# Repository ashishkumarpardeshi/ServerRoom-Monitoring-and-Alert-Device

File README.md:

# ServerRoom-Monitoring-and-Alert-Device

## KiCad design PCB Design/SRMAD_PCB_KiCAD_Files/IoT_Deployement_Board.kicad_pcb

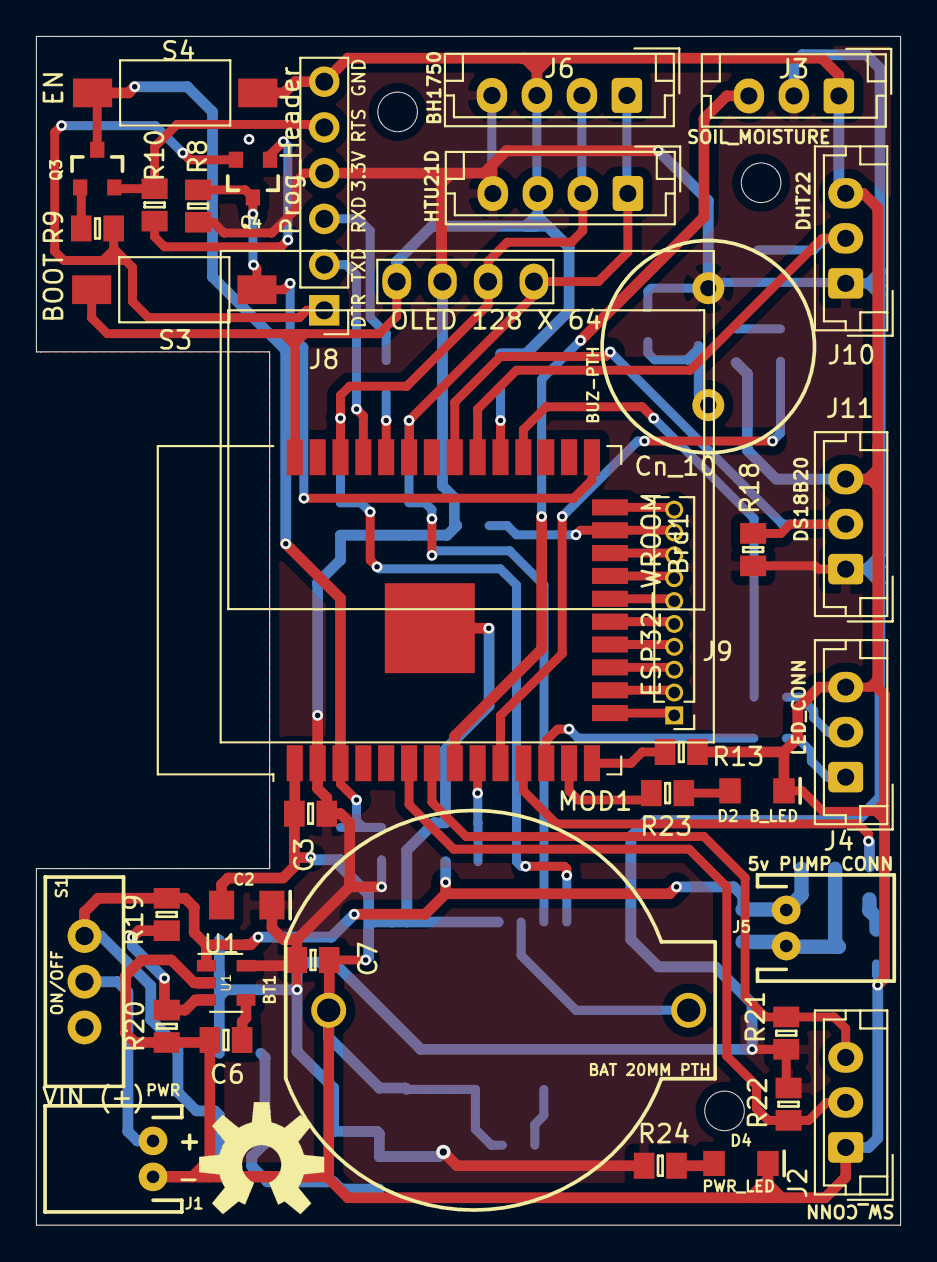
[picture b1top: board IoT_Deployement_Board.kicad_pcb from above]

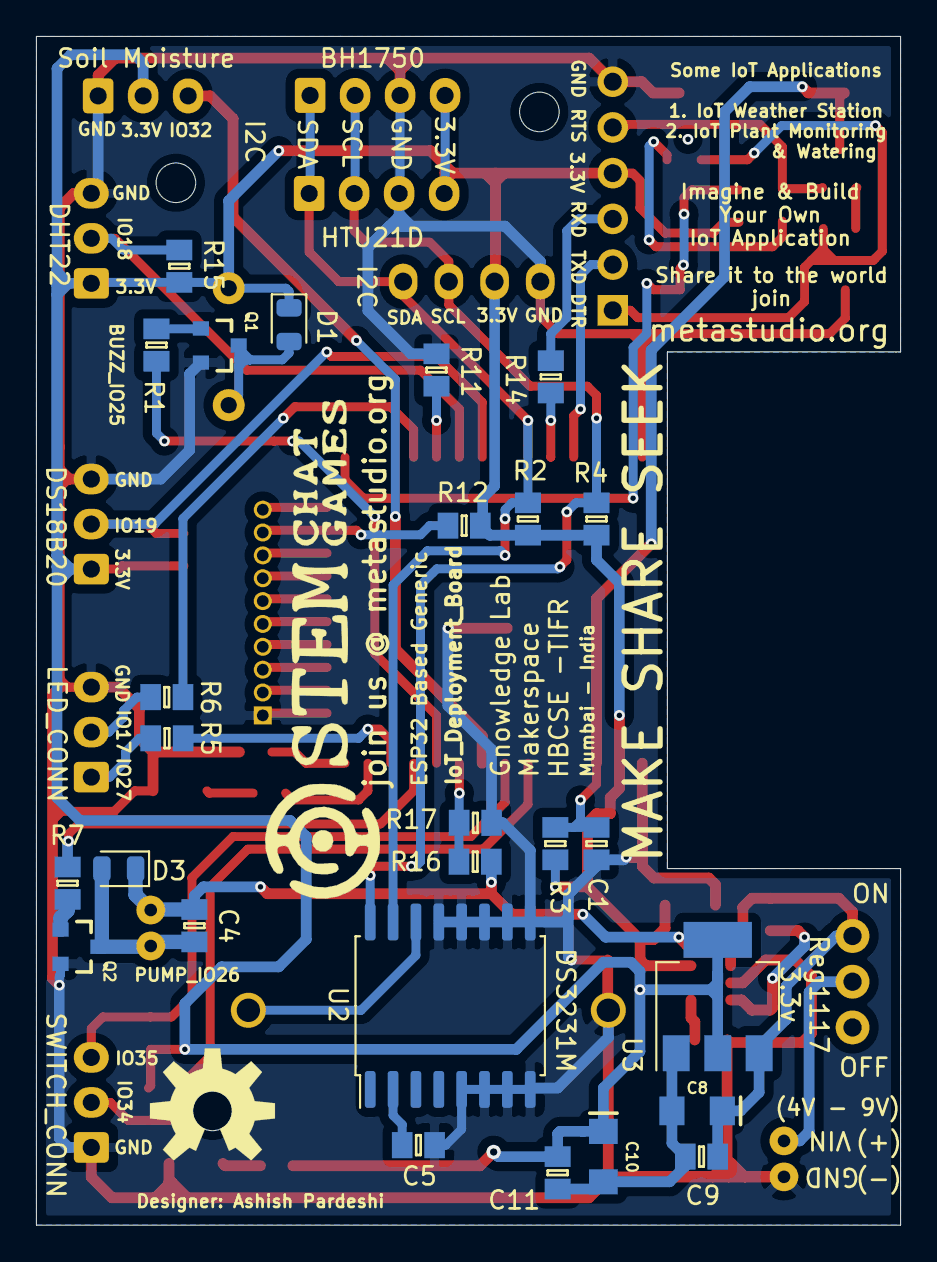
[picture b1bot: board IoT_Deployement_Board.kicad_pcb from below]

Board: 2 copper layers, 48.0 x 66.0 mm, 64 parts (26 on the bottom side), 50 nets.

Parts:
BT1: BAT 20MM PTH; BATTCOM_20MM_PTH
Brd1: SSD1306; 128x64OLED
C1: 1 UF; 0805
C2, C8, C10: 10UF; EIA3216
C3, C4, C5, C9, C11: 0.1 UF; 0805
C6: 470 pF; 0805
C7: 2.2 uF; 0805
D1, D3: 1N4001; D_0805_2012Metric
D2: B_LED; LED-1206
D4: PWR_LED; LED-1206
J1: PWR; JST-2-PTH
J2: Switch_Conn; JST_EH_B3B-EH-A_1x03_P2.50mm_Vertical
J3: Soil_Moisture; JST_EH_B3B-EH-A_1x03_P2.50mm_Vertical
J4: LED_CONN; JST_EH_B3B-EH-A_1x03_P2.50mm_Vertical
J5: Pump_Conn; JST-2-PTH
J6: BH1750; JST_EH_B4B-EH-A_1x04_P2.50mm_Vertical
J7: HTUI2D; JST_EH_B4B-EH-A_1x04_P2.50mm_Vertical
J8: Prog_Header; PinHeader_1x06_P2.54mm_Vertical
J9: Cn_10; PinHeader_1x10_P1.27mm_Vertical
J10: DHT22; JST_EH_B3B-EH-A_1x03_P2.50mm_Vertical
J11: DS18B20; JST_EH_B3B-EH-A_1x03_P2.50mm_Vertical
LS1: BUZ-PTH; BUZZER-12MM
MOD1: ESP32-WROOM; ESP32-WROOM-32
Q1, Q2, Q3, Q4: MMBT2222A2; SOT23-3
R1, R7: 1k; 0805
R2, R3, R4, R8, R9, R10, R11, R12, R13, R15, R18, R21, R22: 10k; 0805
R5, R6, R14, R23, R24: 470e; 0805
R16, R17, R19, R20: 0805
S1: ON/OFF; SWITCH_SPDT_PTH_11.6X4.0MM
S3: Boot; SW_SPST_FSMSM
S4: EN; SW_SPST_FSMSM
U1: MIC5219-3v3; SOT-23-5
U2: DS3231M; SOIC-16W_7.5x10.3mm_P1.27mm
U3: AMS1117-3.3; SOT-223-3_TabPin2

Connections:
3.3V: Brd1.2, C2.+, C3.1, C7.1, C10.+, C11.1, D1.1, J3.2, J6.4, J7.4, J8.4, J10.1, J11.1, LS1.-, MOD1.2, R2.1, R3.1, R4.1, R8.2, R12.2, R15.2, R18.2, R21.2, R22.2, R24.2, U1.5, U3.2
+3V3: C5.1, U2.2
+4V: C4.1, C8.+, C9.1, D3.1, J5.1, R16.2, R19.2, S1.3, U1.1, U3.3
Battery_Voltage: MOD1.9, R16.1, R17.2
Board_LED: MOD1.13, R23.2
Buzz_IO: MOD1.10, R1.1
DHT22: J10.2, MOD1.30, R15.1
DS182B0: J11.2, MOD1.31, R18.1
DTR: J8.1, Q4.2, R9.1
EN: C1.1, MOD1.3, Q3.3, R3.2, S4.1
GND: BT1.2, Brd1.1, C1.2, C2.-, C3.2, C5.2, C6.2, C7.2, D2.C, D4.C, J1.1, J2.1, J3.1, J4.3, J6.3, J7.3, J8.6, J9.1, J10.3, J11.3, MOD1.1, MOD1.15, MOD1.38, MOD1.39, Q1.2, Q2.2, R11.2, R13.2, R17.1, R20.1, S3.2, S4.2, U1.2, U2.5, U2.6, U2.7, U2.8, U2.9, U2.10, U2.11, U2.12, U2.13
IO0: MOD1.25, Q4.3, R8.1, S3.1
LED_1: MOD1.12, R5.1
LED_2: MOD1.28, R6.1
unnamed: BT1.1, U2.14
unnamed: C4.2, D3.2, J5.2, Q2.3
unnamed: C6.1, U1.4
unnamed: C8.-, C9.2, C10.-, C11.2, U3.1
unnamed: D1.2, LS1.+, Q1.3
unnamed: D2.A, R23.1
unnamed: D4.A, R24.1
unnamed: J1.2, S1.2
unnamed: J4.1, R5.2
unnamed: J4.2, R6.2
unnamed: J9.3, MOD1.17
unnamed: J9.4, MOD1.18
unnamed: J9.5, MOD1.19
unnamed: J9.6, MOD1.20
unnamed: J9.7, MOD1.21
unnamed: J9.8, MOD1.22
unnamed: MOD1.14, R13.1
unnamed: MOD1.29, R11.1
unnamed: MOD1.34, R14.2
unnamed: Q1.1, R1.2
unnamed: Q2.1, R7.2
unnamed: Q3.1, R9.2
unnamed: Q4.1, R10.2
unnamed: R19.1, R20.2, U1.3
Pin_16: J9.2, MOD1.16
Pin_23: J9.9, MOD1.23, R12.1
Pin_24: J9.10, MOD1.24
Pump_IO: MOD1.11, R7.1
RTS: J8.5, Q3.2, R10.1
RXD: J8.3, R14.1
SCL: Brd1.3, J6.2, J7.2, MOD1.36, R4.2, U2.16
SDA: Brd1.4, J6.1, J7.1, MOD1.33, R2.2, U2.15
S_Moist_Sensor: J3.3, MOD1.8
Sw_1: J2.3, MOD1.7, R21.1
Sw_2: J2.2, MOD1.6, R22.1
TXD: J8.2, MOD1.35

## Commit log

2021-03-13 Added Enclosure V2 build-in-progress
